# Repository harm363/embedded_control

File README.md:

Mijn opdracht voor het vak embedded control, dit vak word in het 4e jaar gegeven tijdens de opleiding elektrotechniek aan de NHLstenden in leeuwarden.

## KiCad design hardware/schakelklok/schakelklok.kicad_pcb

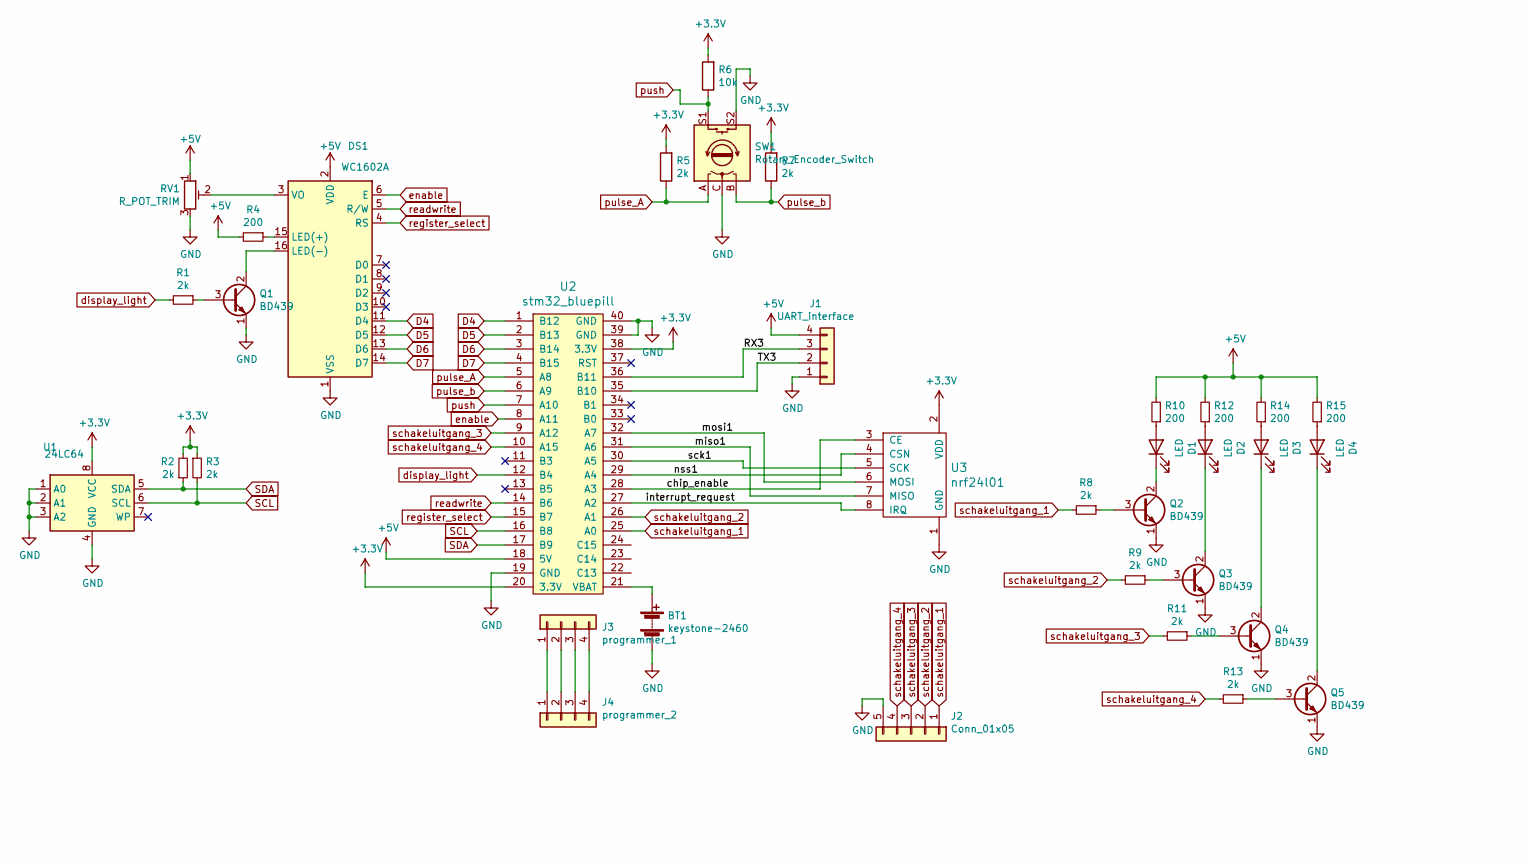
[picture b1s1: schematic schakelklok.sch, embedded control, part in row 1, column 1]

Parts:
BT1: keystone-2460; BatteryHolder_Keystone_2462_2xAA
D1, D2, D3, D4: LED; LED_D5.0mm
DS1: WC1602A; lcd24x2
J1: UART_interface; PinHeader_1x04_P2.54mm_Vertical
J2: Conn_01x05; PinHeader_1x05_P2.54mm_Vertical
J3: programmer_1; PinHeader_1x04_P2.54mm_Vertical
J4: programmer_2; PinHeader_1x04_P2.54mm_Vertical
Q1, Q2, Q3, Q4, Q5: BD439; TO-126-3_Vertical
R1, R2, R3, R5, R7, R8, R9, R11, R13: 2k; Resistor_Horizontal_RM7mm
R4, R10, R12, R14, R15: 200; Resistor_Horizontal_RM7mm
R6: 10k; Resistor_Horizontal_RM7mm
RV1: R_POT_TRIM; Potentiometer_Bourns_3266Y_Vertical
SW1: Rotary_Encoder_Switch; RotaryEncoder_Alps_EC11E-Switch_Vertical_H20mm
U1: 24LC64; DIP-8_W7.62mm_LongPads
U2: stm32_bluepill; DIP-40_W15.24mm_LongPads
U3: nrf24l01

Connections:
+3V3: R2.2, R3.1, R5.2, R6.2, R7.2, U1.8 (VCC), U2.20 (3.3V), U2.38 (3.3V), U3.2 (VDD)
+5V: DS1.2 (VDD), J1.4, R4.2, R10.2, R12.2, R14.2, R15.2, RV1.1, U2.18 (5V)
/RX3: J1.3, U2.36 (B11)
/TX3: J1.2, U2.35 (B10)
/chip_enable: U2.28 (A3), U3.3 (CE)
/interrupt_request: U2.27 (A2), U3.8 (IRQ)
/miso1: U2.31 (A6), U3.7 (MISO)
/mosi1: U2.32 (A7), U3.6 (MOSI)
/nss1: U2.29 (A4), U3.4 (CSN)
/sck1: U2.30 (A5), U3.5 (SCK)
D4: DS1.11 (D4), U2.1 (B12)
D5: DS1.12 (D5), U2.2 (B13)
D6: DS1.13 (D6), U2.3 (B14)
D7: DS1.14 (D7), U2.4 (B15)
GND: BT1.2 (-), DS1.1 (VSS), J1.1, J2.5, Q1.1 (E), Q2.1 (E), Q3.1 (E), Q4.1 (E), Q5.1 (E), RV1.3, SW1.C, SW1.S2, U1.1 (A0), U1.2 (A1), U1.3 (A2), U1.4 (GND), U2.19 (GND), U2.39 (GND), U2.40 (GND), U3.1 (GND)
unnamed: BT1.1 (+), U2.21 (VBAT)
unnamed: D1.1 (K), Q2.2 (C)
unnamed: D1.2 (A), R10.1
unnamed: D2.1 (K), Q3.2 (C)
unnamed: D2.2 (A), R12.1
unnamed: D3.1 (K), Q4.2 (C)
unnamed: D3.2 (A), R14.1
unnamed: D4.1 (K), Q5.2 (C)
unnamed: D4.2 (A), R15.1
unnamed: DS1.3 (VO), RV1.2
unnamed: DS1.15 (LED(+)), R4.1
unnamed: DS1.16 (LED(-)), Q1.2 (C)
unnamed: J3.1, J4.1
unnamed: J3.2, J4.2
unnamed: J3.3, J4.3
unnamed: J3.4, J4.4
unnamed: Q1.3 (B), R1.1
unnamed: Q2.3 (B), R8.1
unnamed: Q3.3 (B), R9.1
unnamed: Q4.3 (B), R11.1
unnamed: Q5.3 (B), R13.1
SCL: R3.2, U1.6 (SCL), U2.16 (B8)
SDA: R2.1, U1.5 (SDA), U2.17 (B9)
display_light: R1.2, U2.12 (B4)
enable: DS1.6 (E), U2.8 (A11)
pulse_A: R5.1, SW1.A, U2.5 (A8)
pulse_b: R7.1, SW1.B, U2.6 (A9)
push: R6.1, SW1.S1, U2.7 (A10)
readwrite: DS1.5 (R/W), U2.14 (B6)
register_select: DS1.4 (RS), U2.15 (B7)
schakeluitgang_1: J2.1, R8.2, U2.25 (A0)
schakeluitgang_2: J2.2, R9.2, U2.26 (A1)
schakeluitgang_3: J2.3, R11.2, U2.9 (A12)
schakeluitgang_4: J2.4, R13.2, U2.10 (A15)

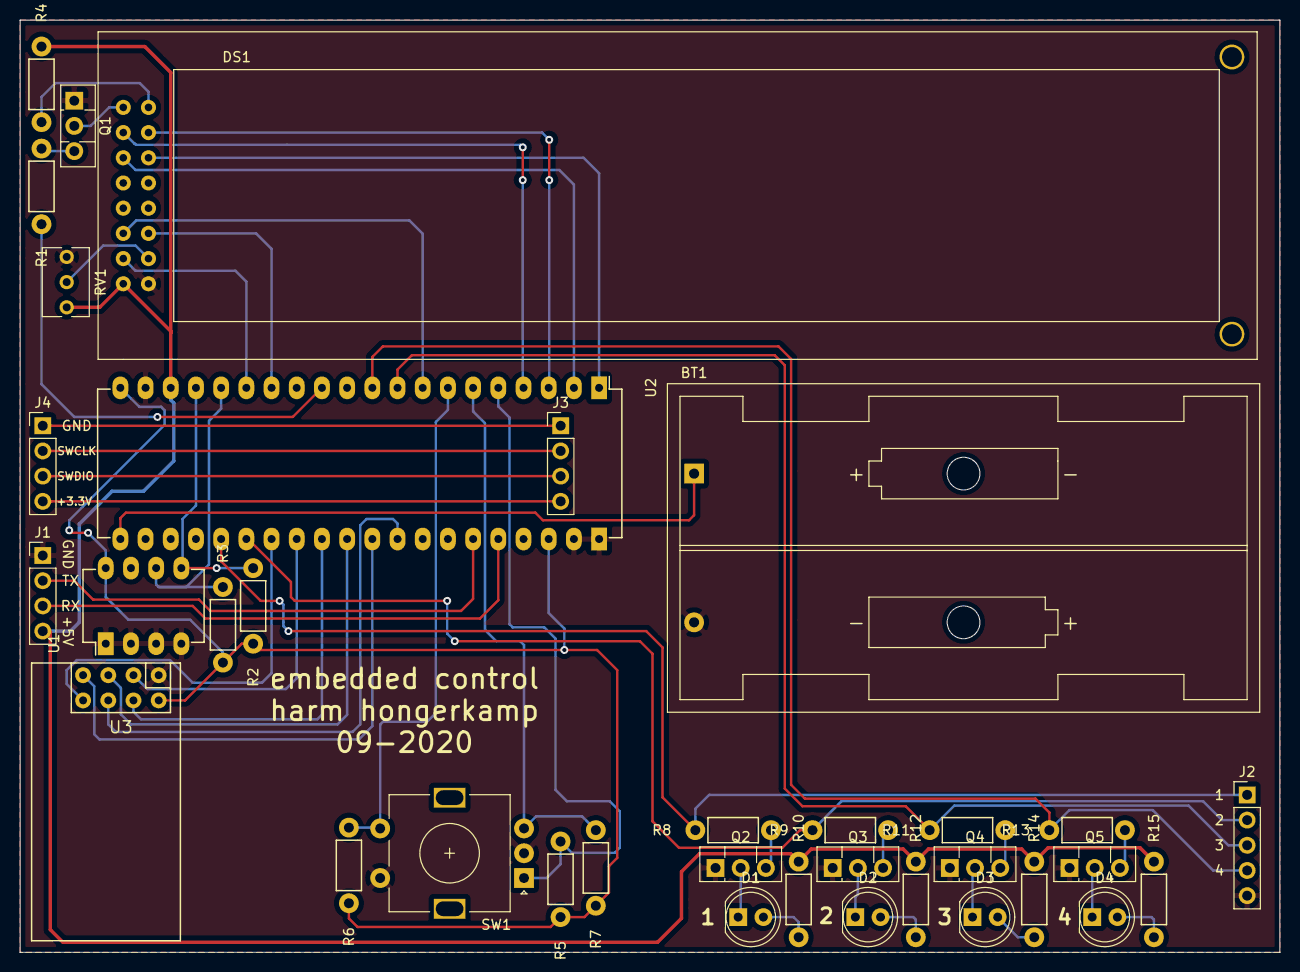
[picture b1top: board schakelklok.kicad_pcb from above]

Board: 2 copper layers, 127.0 x 94.0 mm, 35 parts (0 on the bottom side), 49 nets.

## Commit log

2020-09-12 finished schematic
2020-09-12 started routing
2020-09-12 finished hardware
2020-09-17 added panel
2020-09-23 added gitignore
2020-09-23 gitignore on correct location
2020-10-05 added firmware
